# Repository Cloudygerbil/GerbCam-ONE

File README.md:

# GerbCam ONE

This is A tool to keep an eye on my pet gerbils while I'm away on holiday. It is designed to run on a Raspberry Pi and any old webcam you have collecting dust.

## Hardware

The hardware on this is a simple battery PCB which converts the 12V from 8 AA batteries to 5V for the Raspberry Pi. It could work with 3.7 V lithium-ion cells but is untested.

## Software

The Raspberry Pi runs the motion detecting algorithm which scans every 4th frame for movement and records when motion is found. The Pi also hosts the website

## Instructions

- Make sure to put in your site a password into ddns.sh as I obviously haven't added mine
- Case should be assembled with M3 heat inserts and M3 6mm bolts
- Configure cron to run startup.sh

Onshape URL: https://cad.onshape.com/documents/b9b5efc3e67051879257010d/w/97c2399b92ab84e6df797935/e/d288fcda08a8171d0bd35e9a

BOM:

| Material | Qty | Value |
| --- | --- | --- |
| PLA | 200g | White and Orange |
| LM2596S-5 | 1 | none |
| Inductor | 1 | 33 µH |
| Screw Terminal | 1 | Screw_Terminal_2_P5.00mm |
| Diode | 1 | SR503 |
| Capacitor | 1 | 220 µF |
| Capacitor | 1 | 680 µF |
| AA Batteries holder | 4 | 2 Batteries |
| M3 Bolts | 4 | 6 mm depth |
| M3 Heat inserts | 4 | 4 mm depth |
| Webcam | 1 | USB connector |
| Raspberry Pi Zero W | 1 | null |
| AA Batteries holder | 8 | Should be rechargable |
| USB Female to USB micro male converter | 1 | preferably low profile |

Thank you to hack club for keeping me motivated to finish this.

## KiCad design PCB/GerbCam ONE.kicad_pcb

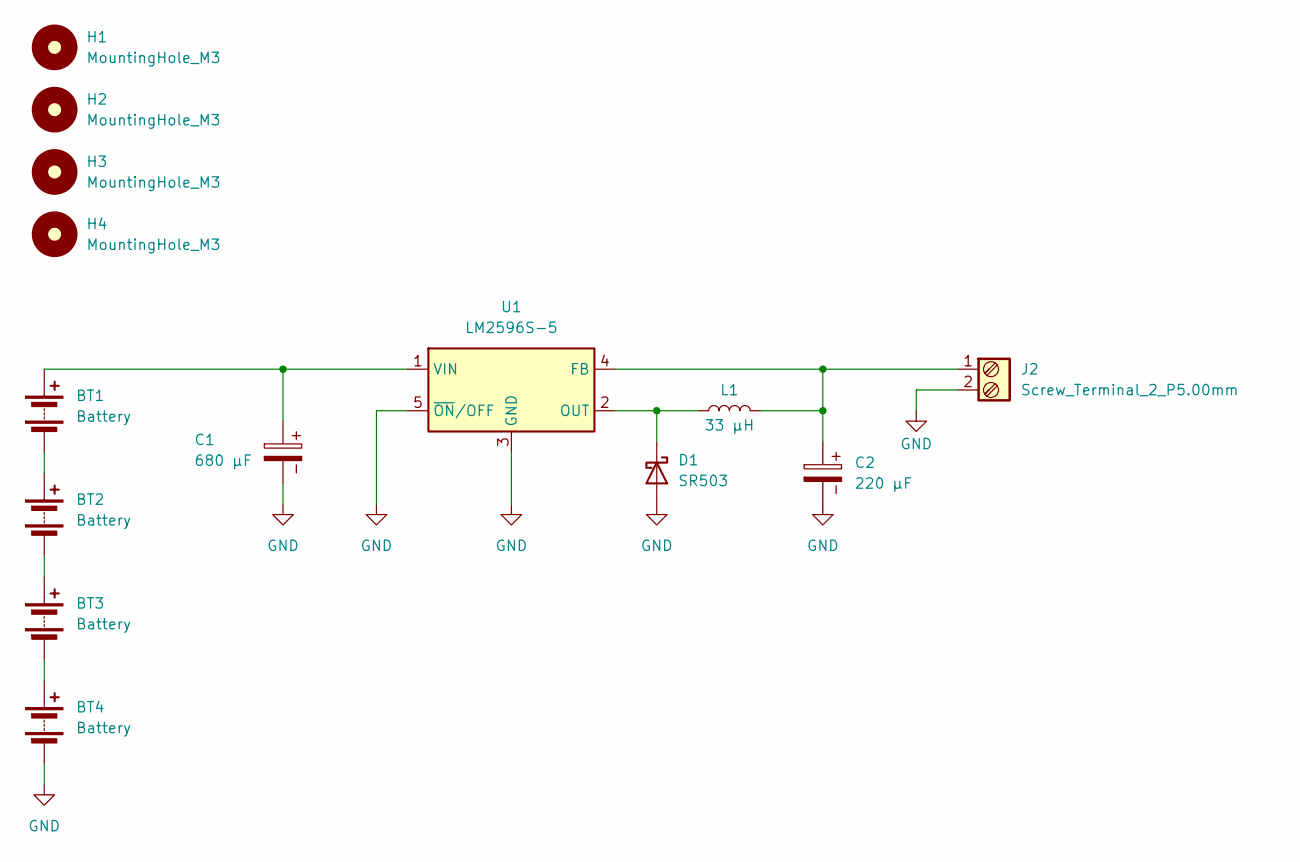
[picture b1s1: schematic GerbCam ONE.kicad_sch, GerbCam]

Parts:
BT1, BT2, BT3, BT4: Battery; BatteryHolder_Keystone_2462_2xAA
C1: 680 µF; CP_Radial_D8.0mm_P3.50mm
C2: 220 µF; CP_Radial_D8.0mm_P3.50mm
D1: SR503; D_DO-201AD_P15.24mm_Horizontal
H1, H2, H3, H4: MountingHole_M3; MountingHole_3.2mm_M3
J2: Screw_Terminal_2_P5.00mm; TerminalBlock_Phoenix_PT-1,5-2-5.0-H_1x02_P5.00mm_Horizontal
L1: 33 µH; Inductor_Radial_D;15_P;10
U1: LM2596S-5; TO-263-5_TabPin3

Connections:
+5V: C2.1, J2.1, L1.2, U1.4 (FB)
+12V: BT1.1 (+), C1.1, U1.1 (VIN)
GND: BT4.2 (-), C1.2, C2.2, D1.2 (A), J2.2, U1.3 (GND), U1.5 (~ON/OFF)
unnamed: BT1.2 (-), BT2.1 (+)
unnamed: BT2.2 (-), BT3.1 (+)
unnamed: BT3.2 (-), BT4.1 (+)
unnamed: D1.1 (K), L1.1, U1.2 (OUT)

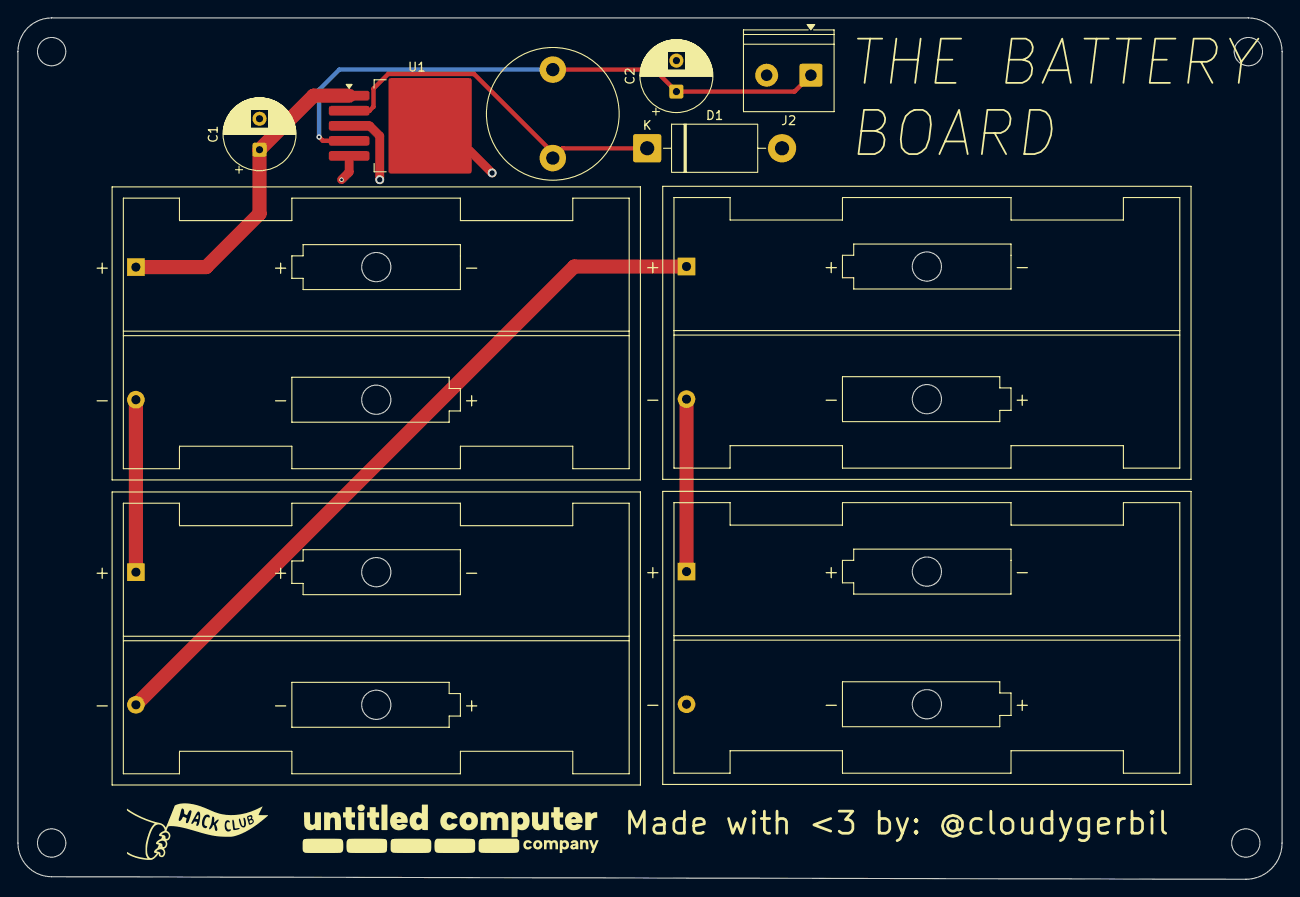
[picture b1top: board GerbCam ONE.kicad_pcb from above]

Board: 2 copper layers, 142.9 x 97.4 mm, 14 parts (0 on the bottom side), 7 nets.

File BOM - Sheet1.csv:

Material,Qty,Value
PLA,200g,White and Orange
LM2596S-5,1,none
Inductor,1,33 µH
Screw Terminal,1,Screw_Terminal_2_P5.00mm
Diode,1,SR503
Capacitor,1,220 µF
Capacitor,1,680 µF
AA Batteries holder,4,2 Batteries
M3 Bolts,4,6 mm depth
M3 Heat inserts,4,4 mm depth
Webcam,1,USB connector
Raspberry Pi Zero W,1,null
AA Batteries holder,8,Should be rechargable

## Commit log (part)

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2026-06-04 Initialize README with placeholder text
2026-06-04 pcb files
2026-06-04 Rename GerbCam ONE.kicad_pcb to Battery_PCB/GerbCam ONE.kicad_pcb
2026-06-07 Rename GerbCam ONE.kicad_pro to Battery_PCB/GerbCam ONE.kicad_pro
2026-06-07 Rename GerbCam ONE.kicad_sch to Battery_PCB/GerbCam ONE.kicad_sch
2026-06-07 Adding everything from software
2026-06-07 Add ASCII art and content to readme.md
